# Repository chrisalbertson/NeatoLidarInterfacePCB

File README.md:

# Neato LIDAR Interface PCB

These are KiCAD design files for an interface PCB for the LIDAR units used in Neato XV-11 and Botvac vacuum cleaners.
This PCB and it's firmware is very much like the open source product sold by GetSurreal.com This version of their idea
uses a less expensive but much more powerfull (STM32 based) plug-in modual and also allows for external power.

This board (with the firmware from my other repository xxx) has the following features:
* Conect to the LIDAR using the native cable on the LIDAR unit
* Connects to any computer using USB.  It enumerates are a serial port.
* controls the speed of the mtor using a PID controller.  I find that regulation is better than 0.5%
* Sends raw LIDAR data over the USB cable
* Implements a simple CLI comand interface for test and dignostics and for setting and storing parameters in the interface's FLASH memory
* This interface board uses a generic STM32F103 (Blue Pill) borad for the comput unit.  These cost $2 on eBay.  Doing this means all the tiny SMD parts are already soldered and you just push the board in as if it were a 40-pid DIP IC.
* This PCB exactly fits in a 3D printable stand I designed.  There are two stands one for XV-11 and one for Botvac.

### jumper pins
Instructions for how to jumpper the board are on the back side silk screen.  Youhave the otopn to use either type LIDAR and to power the LIDAR either from USB or an external 5V power supply.  The external supply would only be required of you are connecting to an unpowered hub. (A 500 mA supply is more than large enough.)

### Which type of LIDAR to use?
Both work equally well but there are differences.
#### XV-11
This unit look the best and is the most compact but it uses a slip ring and mechanical brushes to comutate the data and powert othe spinner scanner.   It seems to work but all mechanical brushes will eventualy fail.
#### Botvac
The blastic base has a ugly looking shape.  But the slip ring has been repalced by a non-contact system.  Power is transmitting using a pair of coils that work like a transformer where the secondary is spinning and the data is send up and down the spin axis by a wiresless (and fiberless) optical link.  The only down side is that this LIDAR uses about down the amount of current.   

### ROADMAP
The processor used here is much faster and has more FLASH memory than the original version.   I plan to use this to enable some more features.  Some of them might be:
* Add a small LCD display to visualize the laser scan data and varify proper operation
* Add a a switch or button to allow simple configuration with no computer connected
* Add a ROS_serial interface mode where the conversion to laser-scan or even point cloud data format is done on theis interface PCB.

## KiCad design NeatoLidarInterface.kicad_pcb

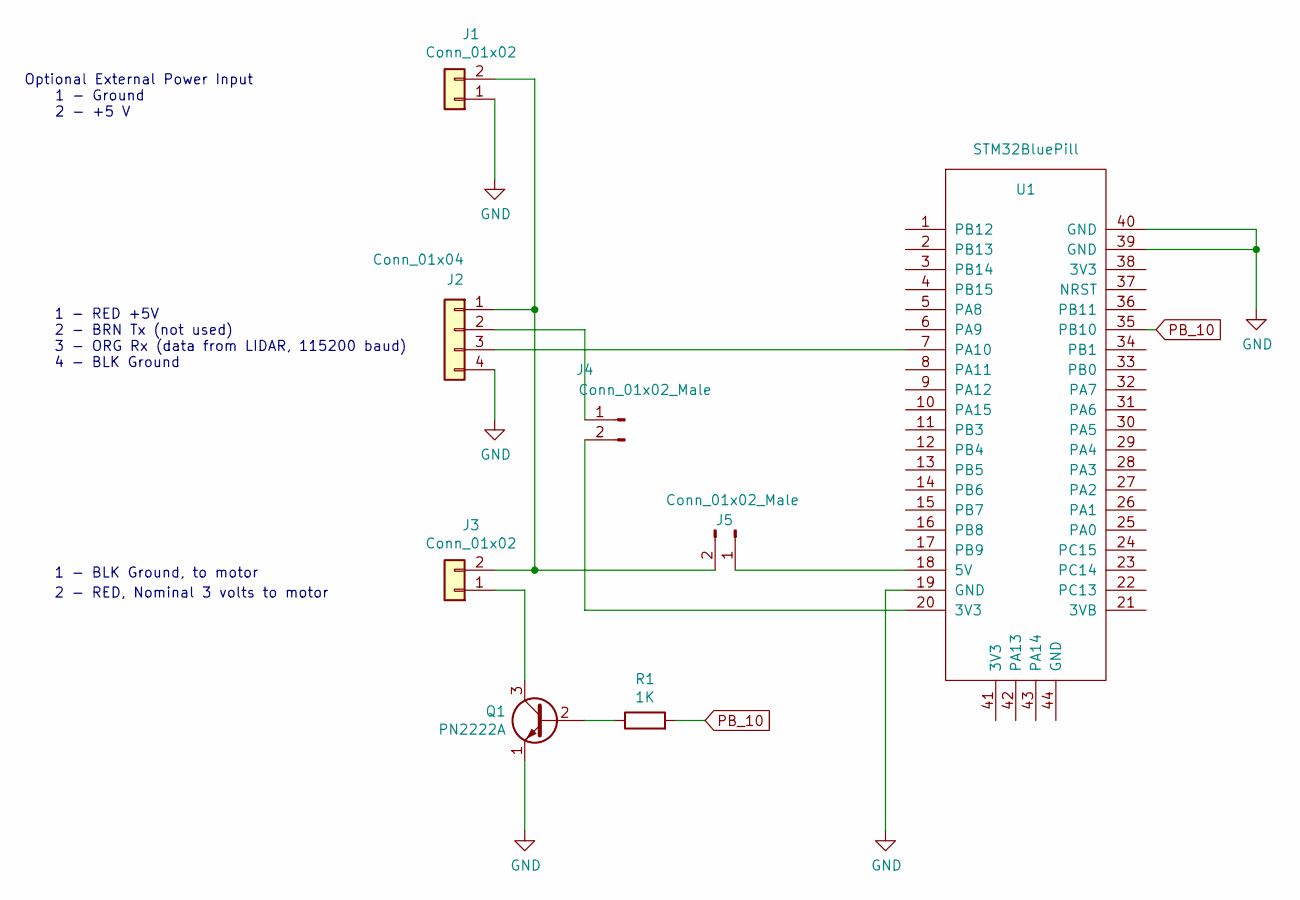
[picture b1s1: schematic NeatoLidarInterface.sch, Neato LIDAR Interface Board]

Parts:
J1, J3: Conn_01x02; JST_JWPF_B02B-JWPF-SK-R_1x02_P2.00mm_Vertical
J2: Conn_01x04; JST_JWPF_B04B-JWPF-SK-R_1x04_P2.00mm_Vertical
J4, J5: Conn_01x02_Male; PinHeader_1x02_P2.54mm_Vertical
Q1: PN2222A; TO-18-3
R1: 1K; R_Axial_DIN0207_L6.3mm_D2.5mm_P7.62mm_Horizontal
U1: STM32BluePill

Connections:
GND: J1.1, J2.4, Q1.1 (E), U1.19 (GND), U1.39 (GND), U1.40 (GND)
unnamed: J1.2, J2.1, J3.2, J5.2
unnamed: J2.2, J4.1
unnamed: J2.3, U1.7 (PA10)
unnamed: J3.1, Q1.3 (C)
unnamed: J4.2, U1.20 (3V3)
unnamed: J5.1, U1.18 (5V)
unnamed: Q1.2 (B), R1.1
PB_10: R1.2, U1.35 (PB10)

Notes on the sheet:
1 - RED +5V 2 - BRN Tx (not used) 3 - ORG Rx (data from LIDAR, 115200 baud) 4 - BLK Ground
1 - BLK Ground, to motor
2 - RED, Nominal 3 volts to motor
Optional External Power Input 1 - Ground 2 - +5 V

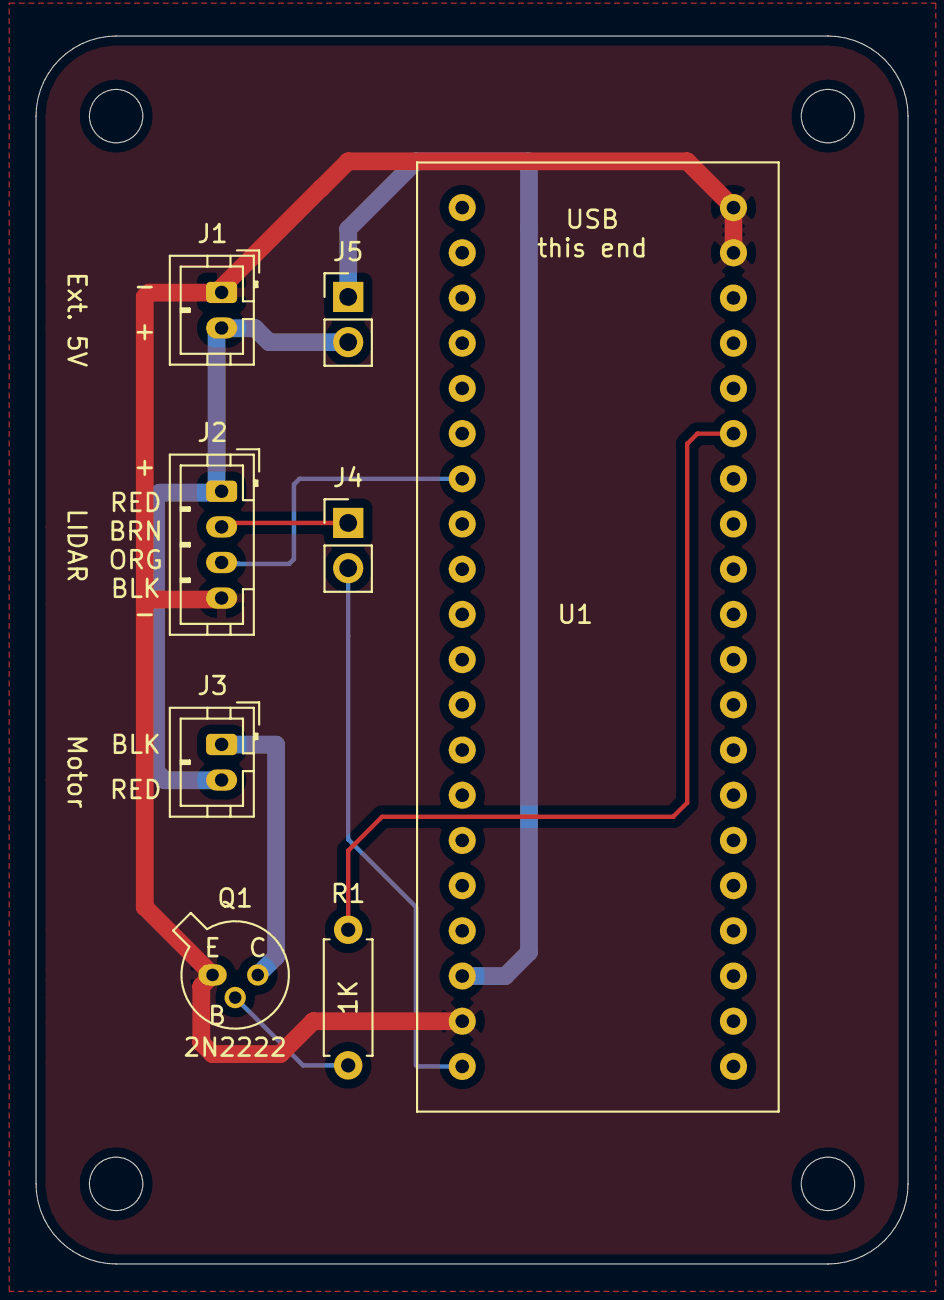
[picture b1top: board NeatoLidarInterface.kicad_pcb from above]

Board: 2 copper layers, 49.0 x 69.0 mm, 8 parts (0 on the bottom side), 9 nets.

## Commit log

2019-06-01 inital checkin
2019-06-01 Update README.md
    Add initial text and image
2019-06-01 Update README.md
    typo
2019-06-01 improve JST footprint, add copper fill
